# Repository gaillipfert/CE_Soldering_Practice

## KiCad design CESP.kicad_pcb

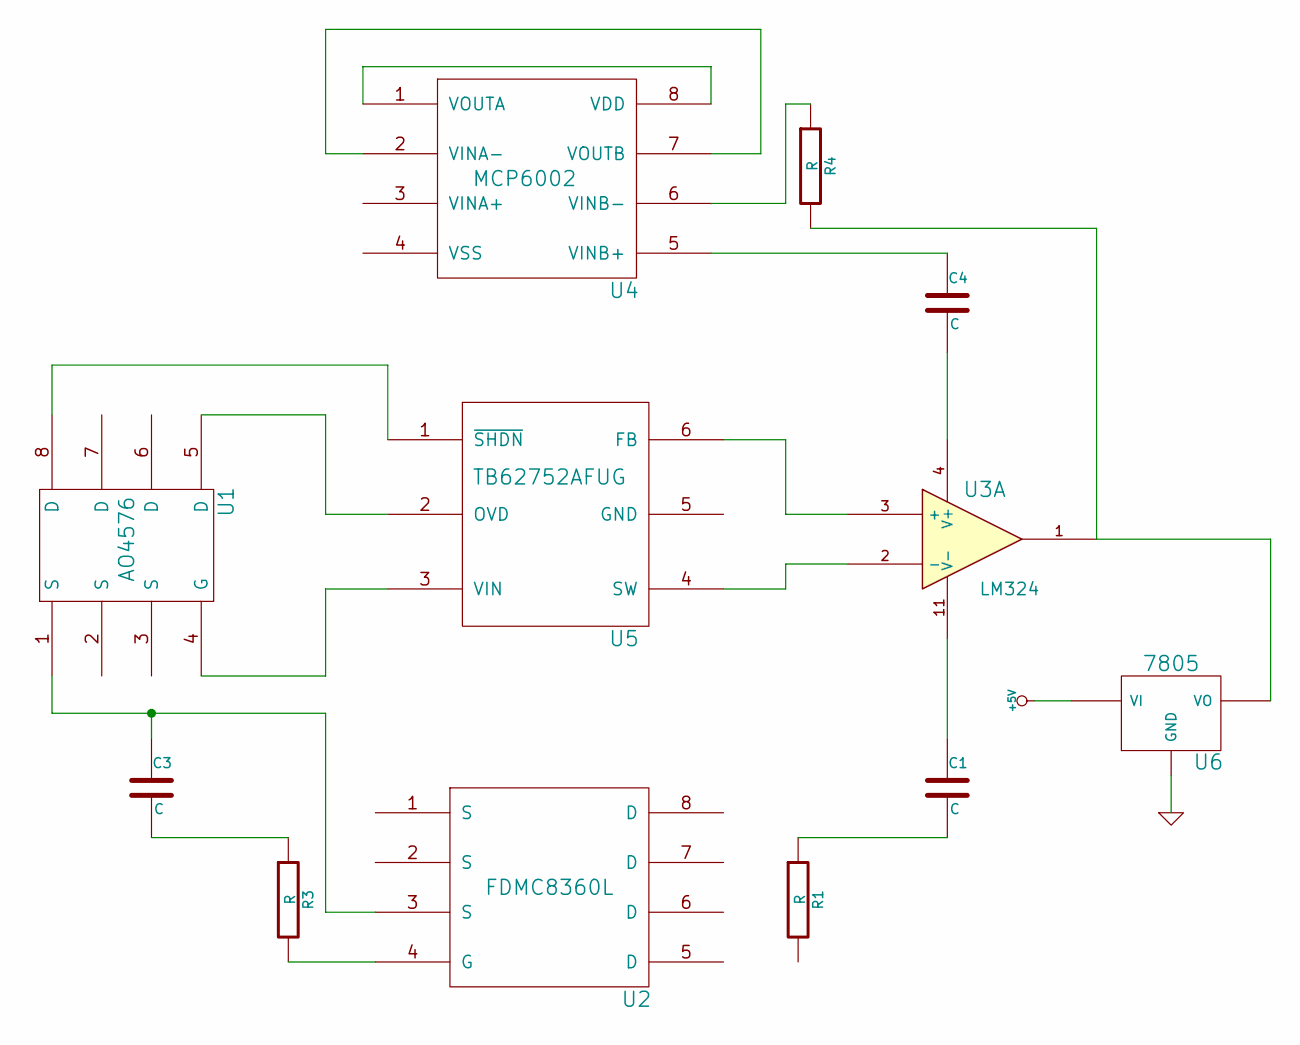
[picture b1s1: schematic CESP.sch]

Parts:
C1, C3, C4: C
R1, R3, R4: R
U1: AO4576
U2: FDMC8360L
U3: LM324
U4: MCP6002
U5: TB62752AFUG
U6: 7805

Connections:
+5V: U6.VI
GND: U6.GND
unnamed: C1.1, U3.11 (V-)
unnamed: C1.2, R1.1
unnamed: C3.1, U1.1 (S), U2.3 (S)
unnamed: C3.2, R3.1
unnamed: C4.1, U4.5 (VINB+)
unnamed: C4.2, U3.4 (V+)
unnamed: R3.2, U2.4 (G)
unnamed: R4.1, U4.6 (VINB-)
unnamed: R4.2, U3.1, U6.VO
unnamed: U1.4 (G), U5.3 (VIN)
unnamed: U1.5 (D), U5.2 (OVD)
unnamed: U1.8 (D), U5.1 (~SHDN)
unnamed: U3.2 (-), U5.4 (SW)
unnamed: U3.3 (+), U5.6 (FB)
unnamed: U4.1 (VOUTA), U4.8 (VDD)
unnamed: U4.2 (VINA-), U4.7 (VOUTB)

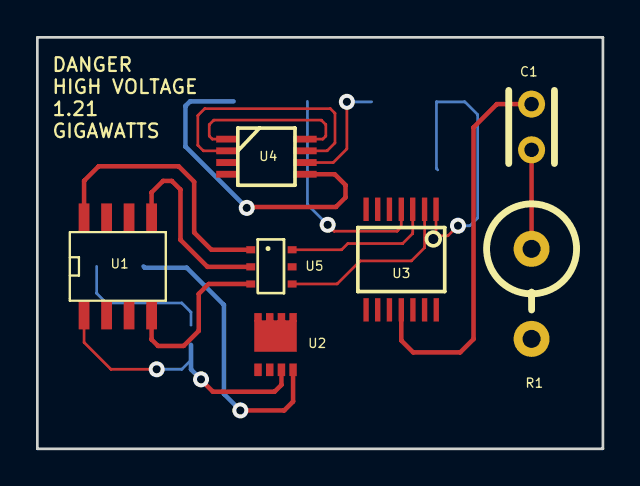
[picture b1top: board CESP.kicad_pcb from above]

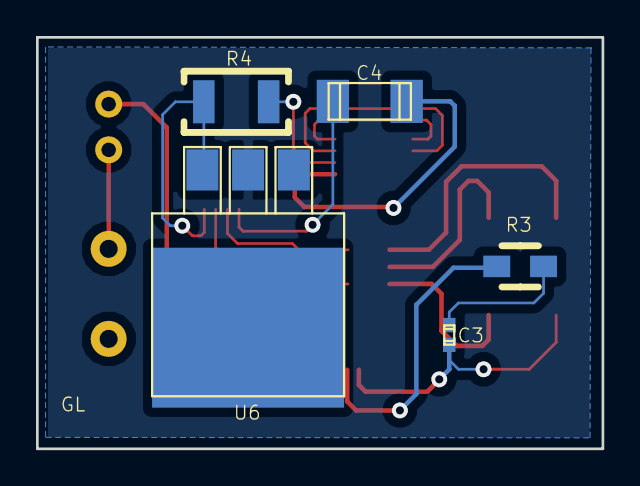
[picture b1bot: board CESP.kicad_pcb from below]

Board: 2 copper layers, 31.4 x 22.9 mm, 12 parts (5 on the bottom side), 16 nets.

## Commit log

2014-01-31 modified: CESP-cache.lib new file: CESP.cmp modified: CESP.kicad_pcb modified: CESP.kicad_pcb-bak new file: CESP.net modified: CESP.pro modified: CESP.sch new file: GLSP.lib new file: GLSP.pretty/DPA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
